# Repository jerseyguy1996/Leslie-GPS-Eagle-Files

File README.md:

Leslie-GPS-Eagle-Files
======================

These are the Eagle Files for the GPS run tracker that I am making for my wife.  It fits neatly into an Altoids Minis Container and includes an OLED display and SD card for logging.  It is still pretty shaky in terms of stability.
.brd and .sch files

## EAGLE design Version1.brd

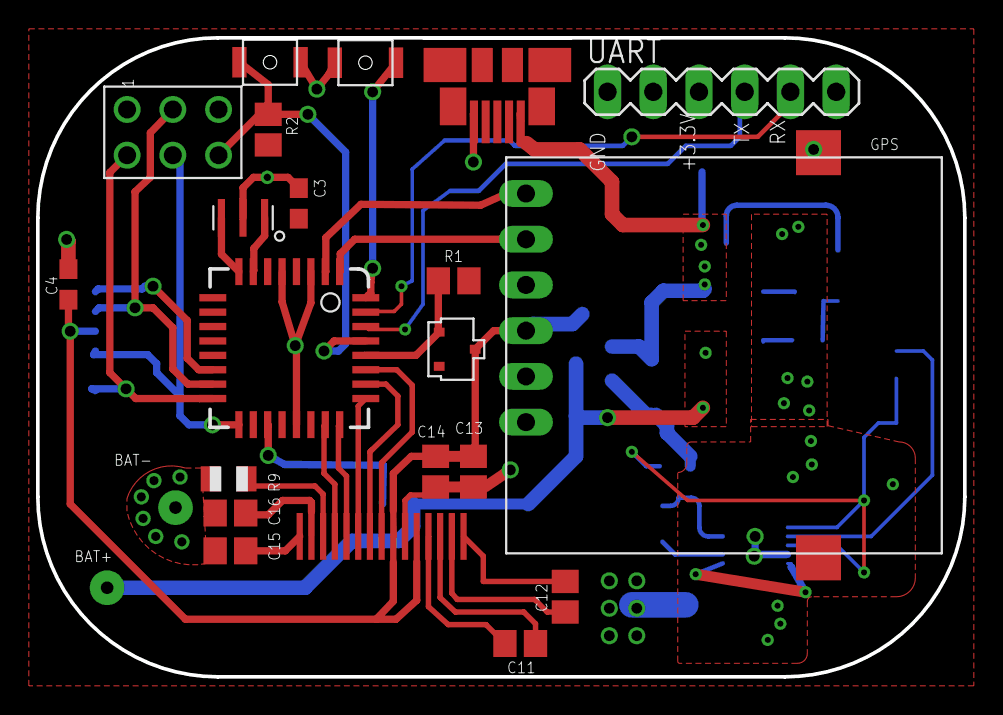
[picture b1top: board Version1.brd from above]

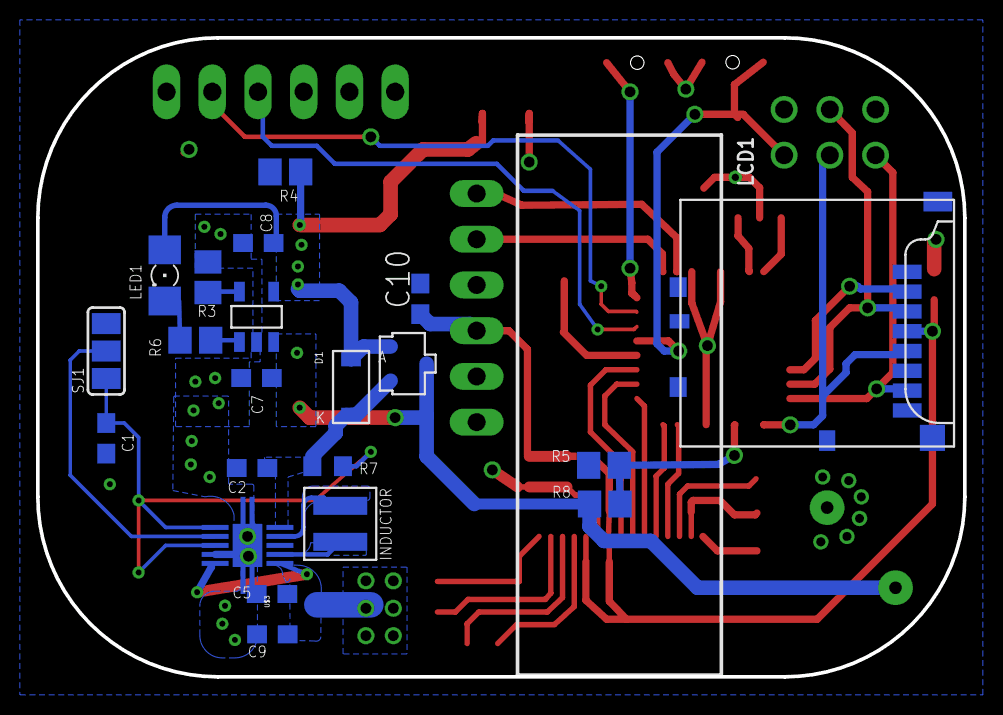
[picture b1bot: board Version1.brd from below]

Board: 2 copper layers, 51.5 x 35.5 mm, 42 parts (22 on the bottom side), 39 nets.

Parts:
C1: .1 uF; C0603
C2, C5, C9: 10 uF; C0603
C3, C4, C10: 10uF; C0603
C7, C8: 4.7uF; C0603
C11, C12, C13, C14: 1 uF; C0805
C15, C16: 2.2 uF; C0805
D1: DB2X20700L; MINI2-F4-B_DIODE
LCD1: UG-2832HSWEG04_WRAPAROUND
LED1: 1206
R1, R2, R4, R8: 10K; R0805
R3: 6.8k; R0805
R5: 30K; R0805
R6: 154; R0805
R7: 100; R0603
R9: 390K; R0805
SJ1: SJ_2
U1: MEGA328; MEGA328-TQFP32
U$2: GPS; FASTRAX_GPS
U$3: TPS63001; SON-10
U$4, U$10: P-Chan; SOT-23
U$5: INDUCTOR; VLS3015E-INDUCTOR
U$6: SD; JA-MICROSD-ST9S008V4AR1500
U$7: ICSP; 2.54MM2X3
U$8: MCP73831T; SOT-23-5
U$9: USB; MOLEX-MICRO-USB-47346-0001
U$12: OSC; MURATA-8MHZ-RESONATOR
U$17: CONTROL; SWITCH-SMALL
U$18: RESET; SWITCH-SMALL
UART: MA06-1

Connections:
+3.3V: C3.1, C5.1, C9.1, R1.1, R2.2, U1.4, U1.6, U1.18, U$2.5, U$3.1, U$3.10, U$4.2, U$7.2, UART.3
AUX_ON: R1.2, U1.28, U$4.1
CONTROL: U1.32, U$17.P$1
GND: C1.2, C2.2, C3.2, C4.2, C5.2, C7.2, C8.2, C9.2, C10.2, C13.1, C14.1, C15.1, C16.1, LCD1.6, R3.1, R4.2, R5.1, R9.2, SJ1.3, U1.3, U1.5, U1.21, U$2.3, U$2.P$7, U$2.P$8, U$3.3, U$3.9, U$3.11, U$3.12, U$3.13, U$3.14, U$3.P$1, U$6.6, U$6.9, U$6.10, U$6.11, U$6.12, U$6.13, U$7.6, U$8.2, U$9.GND, U$12.P$2, U$17.P$2, U$18.P$1, UART.1
GPS_RX: U1.2, U$2.1
GPS_TX: U1.1, U$2.2
L1: U$3.4, U$5.1
L2: U$3.2, U$5.2
unnamed: R3.2, U$8.5
unnamed: U1.7, U$12.P$1
unnamed: U1.8, U$12.P$3
unnamed: R5.2, R8.1, U1.19
unnamed: C11.2, LCD1.4
unnamed: C11.1, LCD1.3
unnamed: SJ1.2, U$3.7
unnamed: C12.1, LCD1.2
unnamed: C12.2, LCD1.1
unnamed: C15.2, LCD1.15
unnamed: C16.2, LCD1.14
unnamed: LCD1.13, R9.1
unnamed: LED1.C, R6.2
unnamed: R6.1, U$8.1
OLED_CLK: LCD1.11, U1.24
OLED_CS: LCD1.8, U1.27
OLED_D/C: LCD1.10, U1.25
OLED_DATA: LCD1.12, U1.23
OLED_RST: LCD1.9, U1.26
RESET: R2.1, U1.29, U$7.5, U$18.P$2
RX: U1.30, UART.4
SD_CLK: U1.17, U$6.5, U$7.3
SD_CS: U1.14, U$6.2
SD_DI: U1.15, U$6.3, U$7.4
SD_DO: U1.16, U$6.7, U$7.1
TX: U1.31, UART.5
VBAT: C7.1, R8.2, U$8.3, U$10.3
VCC_AUX: C4.1, C10.1, C13.2, C14.2, LCD1.5, LCD1.7, U$2.4, U$4.3, U$6.4
VDD: C8.1, D1.ANODE, LED1.A, R4.1, U$8.4, U$9.VCC, U$10.1
VIN: C2.1, D1.CATHODE, R7.2, U$3.5, U$10.2
VINAUX: C1.1, R7.1, SJ1.1, U$3.6, U$3.8

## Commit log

2014-04-19 Version 1
2014-04-21 Minor updates to make the schematic cleaner

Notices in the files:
parts and their libraries:
microbuilder: This work is placed in the public domain, and may be freely used for commercial and non-commercial work with the following conditions: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
